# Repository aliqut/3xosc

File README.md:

# 3xOsc
3xOsc | 3 VCO Eurorack Module

This is a Eurorack format VCO synth module, based on Moritz Klein's VCO design.

The module was designed using KiCad.

---

**Features**:

Each of the 3 oscillators has:
  - Coarse and fine tuning knobs
  - a PWM (Pulse-width Modulation) knob
  - a FM (Frequency Modulation) knob and CV (Control Voltage) input

Controls unique to each oscillator:
- Oscillator 1:
  - Saw/Pulse switch
- Oscillator 2:
  - Saw/Pulse wave mix knob
- Oscillator 3:
  - Saw/Pulse switch
  - PWM modulation input, and modulation amount knob 

# Build Guide

1. Download the Gerber files from each board's '.gerbers' folder.
2. If you want to make any modifications to the schematics, download the schematics, make your modifications, and regenerate new Gerbers
3. View the components required from the `BOM.csv` file. (If you have made any changes to the schematics, it is best to regenerate the BOMs).
4. Order all the components needed
5. Send the Gerber files for PCB manufacturing, you can use [PCBShopper](https://pcbshopper.com/) to compare prices across various manufacturers.
6. Assemble the module

- **Notes**
  - Generic 1/4W 1% resistors will work for the build. 
  - The potentiometers are all linear.
    - For the coarse tuning knobs, you can use logarithmic pots if you prefer.
  - In addition to the components in the BOM, you will need M3 bolts to mount the module into your case, and hex nuts to mount the front panel onto the components (these usually come packaged with all the interface components).

Once you have your PCBs and components, refer to the BOM and schematic to solder the components onto the board.

The module is split into three boards, the main board, the connector board, and the front panel. You can make your own front panel if you'd prefer. 

The front panel board has no electrical connections and is purely aesthetic. I recommend letting your PCB manufacturer know this to avoid any issues.

The main and connector board are connected via the pin headers on the top and bottom of the PCBs, make sure you orient the pin headers properly before soldering. The front panel is secured onto the connector board using hex nuts.

### Front Panel

_To view the front panel on KiCad, you need to install the fonts in the `fonts/` folder from this repo, or replace them with your font of choice._

To get the shiny gold finish for the exposed copper used for text/graphics, make sure you get your PCB manufactured with an ENIG finish. Most PCB manufacturers offer this as an option.

I went for a black solder mask, but you get the option to choose from many different colours when ordering your PCB.

# Contributing

Pull requests are the best way to propose changes to the schematics.

1. Fork the repo and create your branch from `master`.
2. Make your changes to the design.
3. If your change directly affects the module's functionality, update the documentation.
4. Issue pull request

## Any contributions you make will be under the GPL Software License

In short, when you submit code changes, your submissions are understood to be under the same GPL license that covers the project.

## Report issues using Github's Issues tab.

I use GitHub issues to track public bugs. Report a bug by opening a new issue.

**Issue Reports** tend to have:

- A quick summary and/or background
- Steps to reproduce
  - Be specific
- What you expected would happen
- What actually happens
- Notes (possibly including why you think this might be happening, or stuff you tried that didn't work)

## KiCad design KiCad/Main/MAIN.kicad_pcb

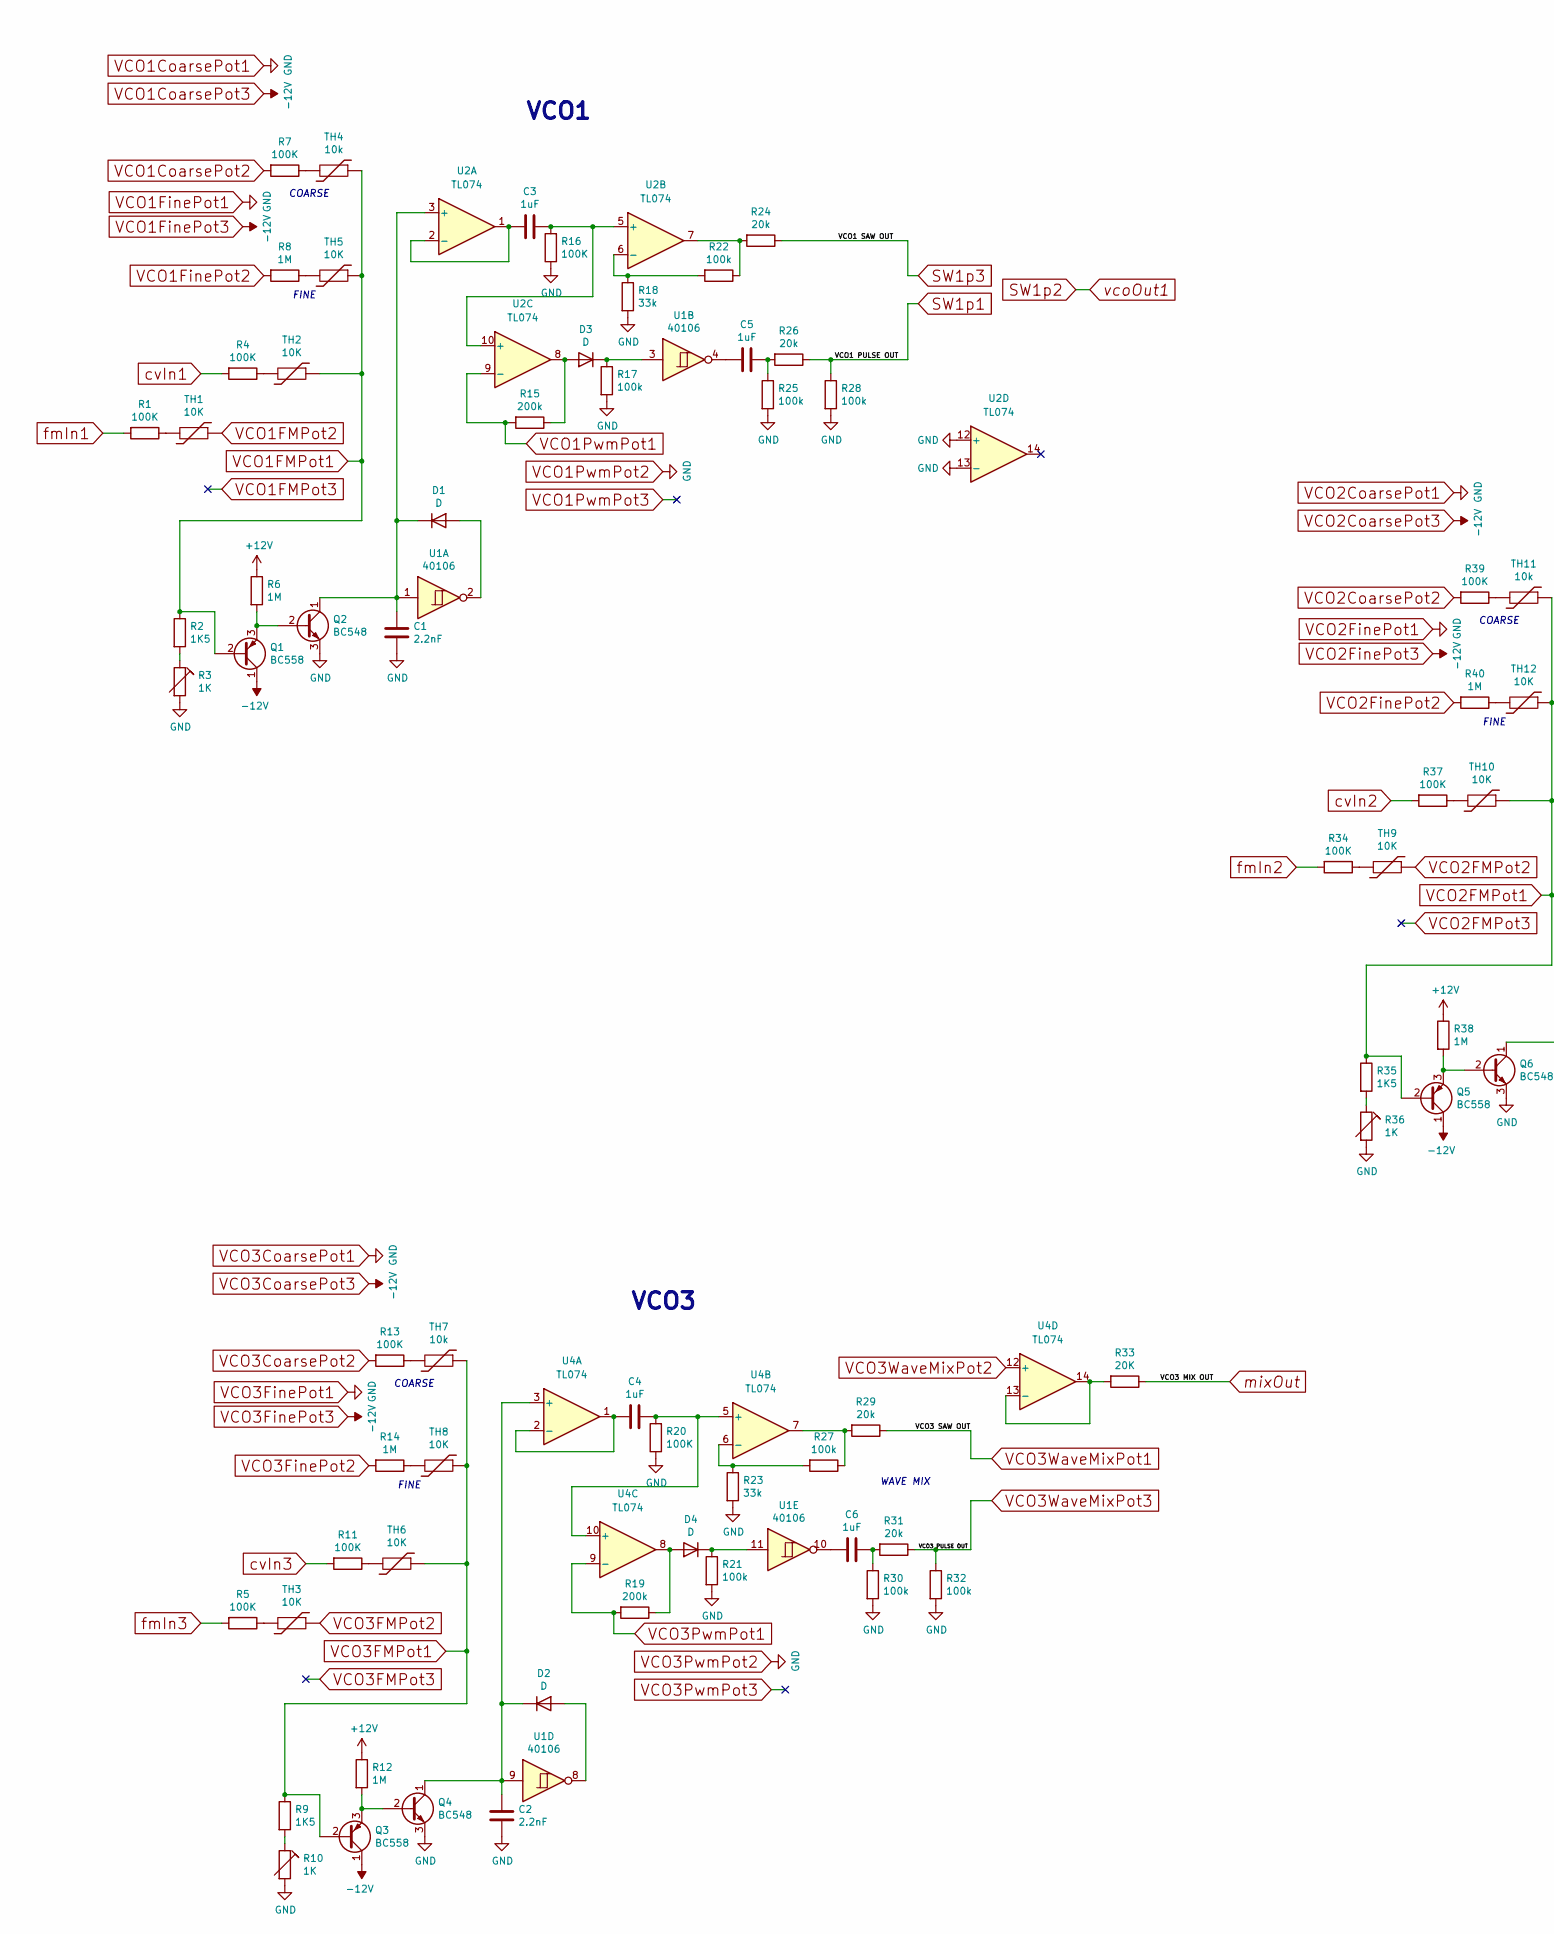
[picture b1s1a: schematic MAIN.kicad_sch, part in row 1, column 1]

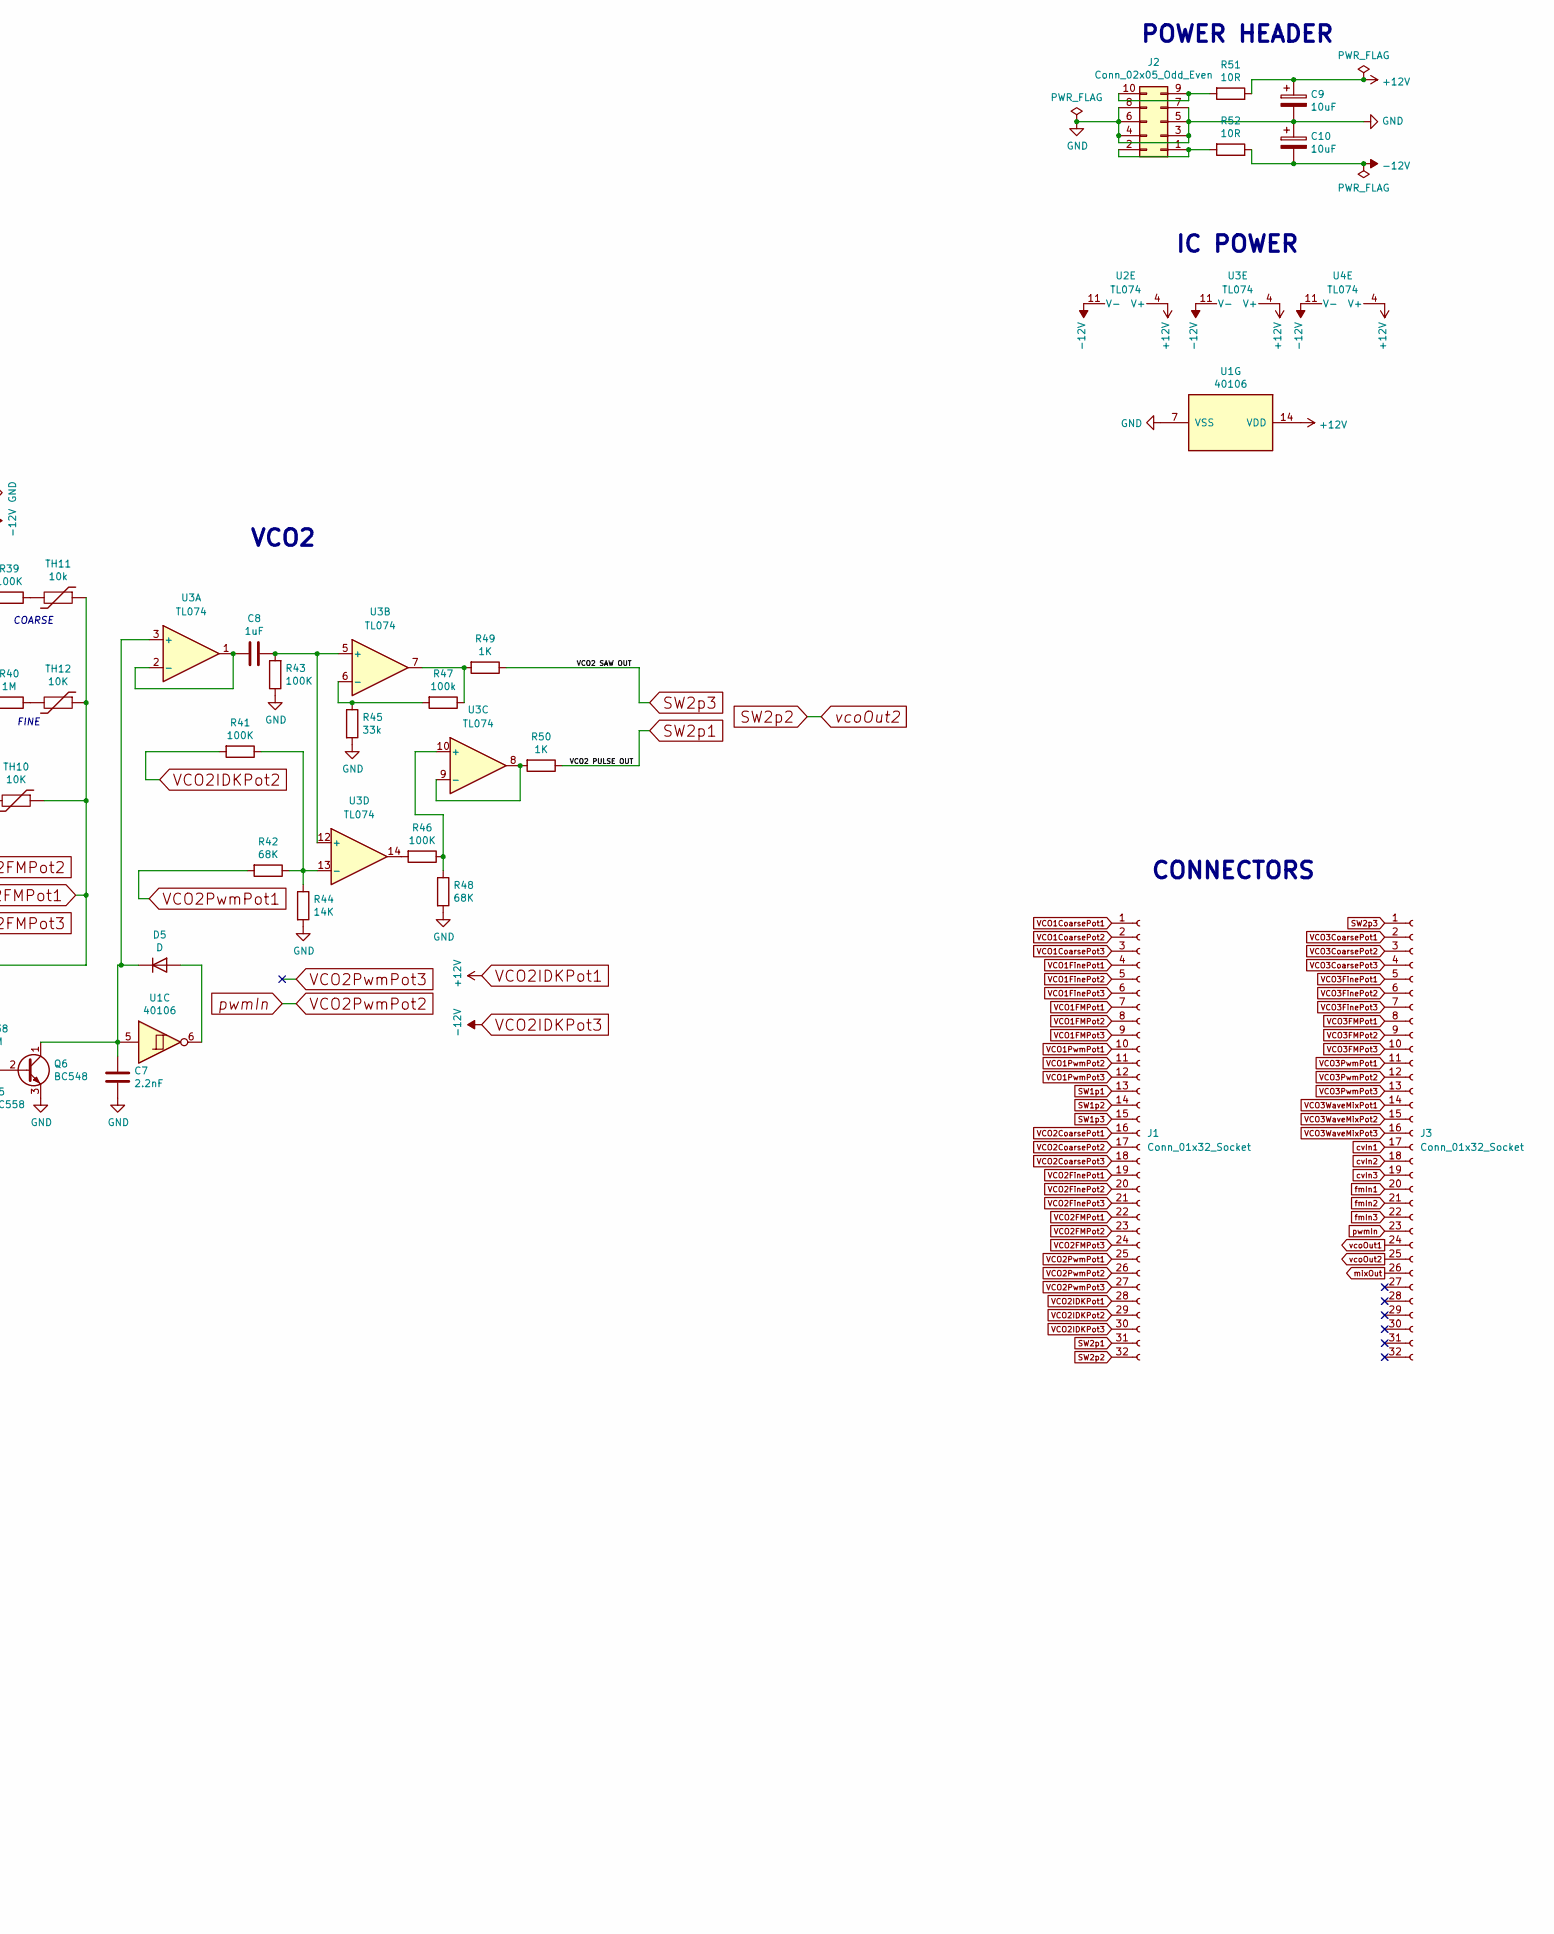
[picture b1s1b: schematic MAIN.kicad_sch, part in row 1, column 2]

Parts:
C1, C2, C7: 2.2nF; C_Disc_D4.7mm_W2.5mm_P5.00mm
C3, C4, C5, C6, C8: 1uF; C_Disc_D3.0mm_W1.6mm_P2.50mm
C9, C10: 10uF; CP_Radial_D5.0mm_P2.00mm
D1, D2, D3, D4, D5: D; D_DO-15_P5.08mm_Vertical_AnodeUp
J1, J3: Conn_01x32_Socket; PinHeader_1x32_P2.54mm_Vertical
J2: Conn_02x05_Odd_Even; PinHeader_2x05_P2.54mm_Vertical
Q1, Q3, Q5: BC558; TO-92_Inline
Q2, Q4, Q6: BC548; TO-92_Inline
R1, R4, R5, R7, R11, R13, R16, R20, R34, R37, R39, R41, R43, R46: 100K; R_Axial_DIN0309_L9.0mm_D3.2mm_P12.70mm_Horizontal
R2, R9, R35: 1K5; R_Axial_DIN0207_L6.3mm_D2.5mm_P10.16mm_Horizontal
R3, R10, R36: 1K; Potentiometer_Bourns_3006Y_Horizontal
R6, R8, R12, R14, R38, R40: 1M; R_Axial_DIN0207_L6.3mm_D2.5mm_P7.62mm_Horizontal
R15, R19: 200k; R_Axial_DIN0207_L6.3mm_D2.5mm_P10.16mm_Horizontal
R17, R21, R22, R25, R27, R28, R30, R32, R47: 100k; R_Axial_DIN0309_L9.0mm_D3.2mm_P12.70mm_Horizontal
R18, R23, R45: 33k; R_Axial_DIN0207_L6.3mm_D2.5mm_P10.16mm_Horizontal
R24, R26, R29, R31: 20k; R_Axial_DIN0207_L6.3mm_D2.5mm_P7.62mm_Horizontal
R33: 20K; R_Axial_DIN0207_L6.3mm_D2.5mm_P7.62mm_Horizontal
R42, R48: 68K; R_Axial_DIN0207_L6.3mm_D2.5mm_P10.16mm_Horizontal
R44: 14K; R_Axial_DIN0207_L6.3mm_D2.5mm_P10.16mm_Horizontal
R49, R50: 1K; R_Axial_DIN0207_L6.3mm_D2.5mm_P10.16mm_Horizontal
R51, R52: 10R; R_Axial_DIN0207_L6.3mm_D2.5mm_P10.16mm_Horizontal
TH1, TH2, TH3, TH5, TH6, TH8, TH9, TH10, TH12: 10K; R_Axial_DIN0204_L3.6mm_D1.6mm_P2.54mm_Vertical
TH4, TH7, TH11: 10k; R_Axial_DIN0204_L3.6mm_D1.6mm_P2.54mm_Vertical
U1: 40106; DIP-14_W7.62mm_Socket
U2, U3, U4: TL074; DIP-14_W7.62mm_Socket

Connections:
unnamed: C5.1, R25.1, R26.2
unnamed: C5.2, U1.4
unnamed: C6.1, R30.1, R31.2
unnamed: C6.2, U1.10
unnamed: D1.2 (A), U1.2
unnamed: C1.1, D1.1 (K), Q2.1 (C), U1.1, U2.3 (+)
unnamed: D2.2 (A), U1.8
unnamed: C2.1, D2.1 (K), Q4.1 (C), U1.9, U4.3 (+)
unnamed: D3.2 (A), R15.1, U2.8
unnamed: D3.1 (K), R17.1, U1.3
unnamed: D4.2 (A), R19.1, U4.8
unnamed: D4.1 (K), R21.1, U1.11
unnamed: D5.2 (A), U1.6
unnamed: C7.1, D5.1 (K), Q6.1 (C), U1.5, U3.3 (+)
unnamed: J2.1, J2.2, R52.2
unnamed: J2.9, J2.10, R51.2
unnamed: Q1.3 (E), Q2.2 (B), R6.2
unnamed: Q3.3 (E), Q4.2 (B), R12.2
unnamed: Q5.3 (E), Q6.2 (B), R38.2
unnamed: R1.1, TH1.2
unnamed: R2.2, R3.1
unnamed: R4.1, TH2.2
unnamed: R5.1, TH3.2
unnamed: R7.1, TH4.2
unnamed: R8.1, TH5.2
unnamed: R9.2, R10.1
unnamed: R11.1, TH6.2
unnamed: R13.1, TH7.2
unnamed: R14.1, TH8.2
unnamed: R22.1, R24.2, U2.7
unnamed: R27.1, R29.2, U4.7
unnamed: R34.1, TH9.2
unnamed: R35.2, R36.1
unnamed: R37.1, TH10.2
unnamed: R39.1, TH11.2
unnamed: R40.1, TH12.2
unnamed: R46.2, U3.14
unnamed: R47.1, R49.2, U3.7
unnamed: C3.2, U2.1, U2.2 (-)
unnamed: C3.1, R16.2, U2.5 (+), U2.10 (+)
unnamed: R18.1, R22.2, U2.6 (-)
unnamed: C8.2, U3.1, U3.2 (-)
unnamed: C8.1, R43.2, U3.5 (+), U3.12 (+)
unnamed: R45.1, R47.2, U3.6 (-)
unnamed: R46.1, R48.1, U3.10 (+)
unnamed: R50.2, U3.8, U3.9 (-)
unnamed: R41.1, R42.1, R44.1, U3.13 (-)
unnamed: C4.2, U4.1, U4.2 (-)
unnamed: C4.1, R20.2, U4.5 (+), U4.10 (+)
unnamed: R23.1, R27.2, U4.6 (-)
unnamed: R33.2, U4.13 (-), U4.14
SW1p1: J1.13, R26.1, R28.1
SW1p2: J1.14, J3.24
SW1p3: J1.15, R24.1
SW2p1: J1.31, R50.1
SW2p2: J1.32, J3.25
SW2p3: J3.1, R49.1
VCO1CoarsePot1: C1.2, C2.2, C7.2, C9.2, C10.1, J1.1, J1.4, J1.11, J1.16, J1.19, J2.3, J2.4, J2.5, J2.6, J2.7, J2.8, J3.2, J3.5, J3.12, Q2.3 (E), Q4.3 (E), Q6.3 (E), R3.2, R10.2, R16.1, R17.2, R18.2, R20.1, R21.2, R23.2, R25.2, R28.2, R30.2, R32.2, R36.2, R43.1, R44.2, R45.2, R48.2, U1.7 (VSS), U2.12 (+), U2.13 (-)
VCO1CoarsePot2: J1.2, R7.2
VCO1CoarsePot3: C10.2, J1.3, J1.6, J1.18, J1.21, J1.30, J3.4, J3.7, Q1.1 (C), Q3.1 (C), Q5.1 (C), R52.1, U2.11 (V-), U3.11 (V-), U4.11 (V-)
VCO1FMPot1: J1.7, Q1.2 (B), R2.1, TH2.1, TH4.1, TH5.1
VCO1FMPot2: J1.8, TH1.1
VCO1FMPot3: J1.9
VCO1FinePot2: J1.5, R8.2
VCO1PwmPot1: J1.10, R15.2, U2.9 (-)
VCO1PwmPot3: J1.12
VCO2CoarsePot2: J1.17, R39.2
VCO2FMPot1: J1.22, Q5.2 (B), R35.1, TH10.1, TH11.1, TH12.1
VCO2FMPot2: J1.23, TH9.1
VCO2FMPot3: J1.24
VCO2FinePot2: J1.20, R40.2
VCO2IDKPot1: C9.1, J1.28, R6.1, R12.1, R38.1, R51.1, U1.14 (VDD), U2.4 (V+), U3.4 (V+), U4.4 (V+)
VCO2IDKPot2: J1.29, R41.2
VCO2PwmPot1: J1.25, R42.2
VCO2PwmPot2: J1.26, J3.23
VCO2PwmPot3: J1.27
VCO3CoarsePot2: J3.3, R13.2
VCO3FMPot1: J3.8, Q3.2 (B), R9.1, TH6.1, TH7.1, TH8.1
VCO3FMPot2: J3.9, TH3.1
VCO3FMPot3: J3.10
VCO3FinePot2: J3.6, R14.2
VCO3PwmPot1: J3.11, R19.2, U4.9 (-)
VCO3PwmPot3: J3.13
VCO3WaveMixPot1: J3.14, R29.1
VCO3WaveMixPot2: J3.15, U4.12 (+)
VCO3WaveMixPot3: J3.16, R31.1, R32.1
cvIn1: J3.17, R4.2
cvIn2: J3.18, R37.2
cvIn3: J3.19, R11.2
fmIn1: J3.20, R1.2
fmIn2: J3.21, R34.2
fmIn3: J3.22, R5.2
mixOut: J3.26, R33.1

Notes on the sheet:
WAVE MIX
COARSE
VCO1
FINE
VCO3
IC POWER
POWER HEADER
CONNECTORS
VCO2

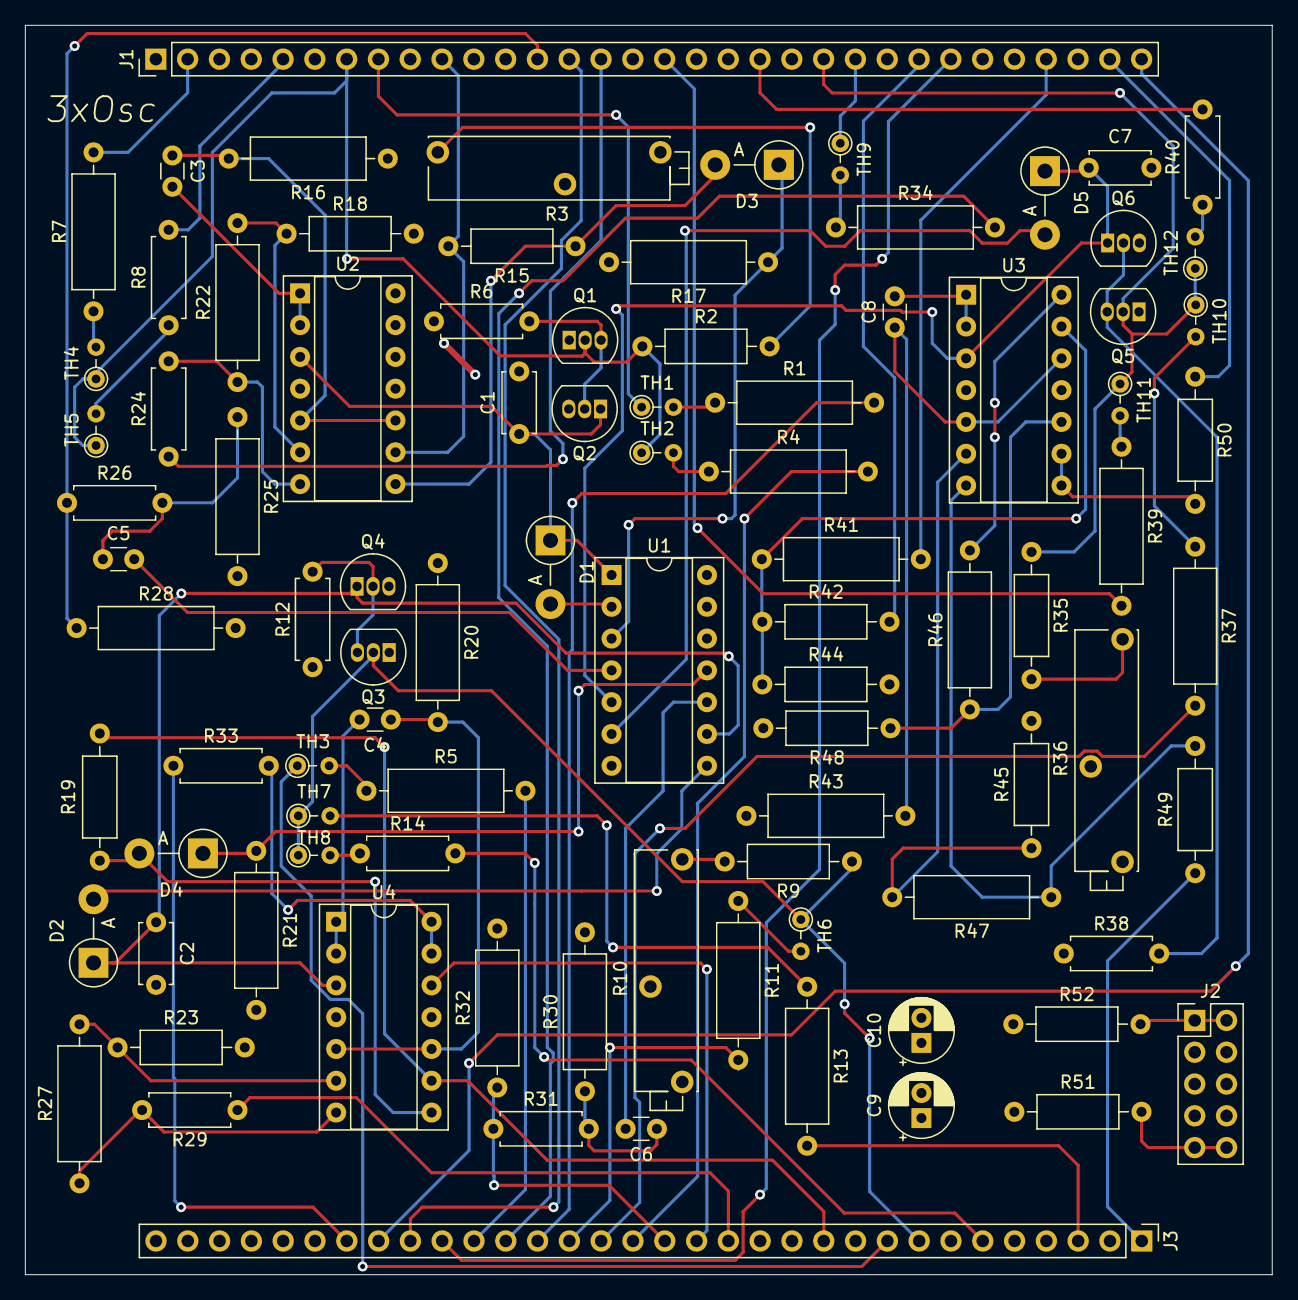
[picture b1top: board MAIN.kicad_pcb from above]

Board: 4 copper layers, 99.6 x 99.8 mm, 92 parts (0 on the bottom side), 87 nets.

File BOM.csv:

MAIN BOARD,,,,,
#,Reference,Qty,Value,Component/Footprint,Notes
1,"C1, C2, C7",3,2.2nF,Disc capacitor: D4.7mm_W2.5mm_P5.00mm,All components are through hole
2,"C3, C4, C5, C6, C8",5,1uF,Disc capacitor: D3.0mm_W1.6mm_P2.50mm,
3,"C9, C10",2,10uF,Electrolitic capacitor :CP_Radial_D5.0mm_P2.00mm,
4,"D1, D2, D3, D4, D5",5,DO-15,DO-15 P5.08mm Vertical AnodeUp,
5,"J1, J3",2,Conn 01x32 Socket,Connector_PinHeader_2.54mm:PinHeader 1x32,Buy a pair of male and female headers. This is for connecting the main board to the connector board.
6,J2,1,Conn 02x05 Odd_Even,Connector_PinHeader_2.54mm:PinHeader 2x05,"Eurorack power header, keyed box 02x05 pin header"
7,"Q1, Q3, Q5",3,BC558 Transistor,THT TO-92_Inline,
8,"Q2, Q4, Q6",3,BC548 Transistor,THT TO-92_Inline,
9,"R1, R4, R5, R7, R11, R13, R16, R20, R34, R37, R39, R41, R43, R46, R17, R21, R22, R25, R27, R28, R30, R32, R47",23,100K,Metalic film resistor 1/4W L9.0mm_D3.2mm_P12.70mm_Horizontal,
10,"R2, R9, R35",3,1K5,Metalic film resistor 1/4W L6.3mm_D2.5mm_P10.16mm_Horizontal,
11,"R3, R10, R36",3,1K,Potentiometer Bourns 3006Y Horizontal,
12,"R6, R8, R12, R14, R38, R40",6,1M,Metalic film resistor 1/4W,
13,"R15, R19",2,200K,Metalic film resistor 1/4W,
14,"R18, R23, R45",3,33K,Metalic film resistor 1/4W,
15,"R24, R26, R29, R31, R33",5,20K,Metalic film resistor 1/4W,
16,"R42, R48",2,68K,Metalic film resistor 1/4W,
17,R44,1,14K,Metalic film resistor 1/4W,
18,"R49, R50",2,1K,Metalic film resistor 1/4W,
19,"R51, R52",2,10R,Metalic film resistor 1/4W,
20,"TH1, TH2, TH3, TH5, TH6, TH8, TH9, TH10, TH12, TH4, TH7, TH11",12,10K,Disk NTC Thermistor,
21,U1,1,40106,40106 Schmitt Trigger Inverter IC THT,
22,"U2, U3, U4",3,TL074,TL074 Op-Amp IC THT,
,,,,,
,,,,,
,,,,,
,,,,,
CONNECTOR BOARD,,,,,
#,Reference,Qty,Value,,Notes
1,"J1, J2",2,Conn_01x32_Socket,2.54mm 01x32,
2,"J3, J4, J5, J6, J7, J8, J9, J10, J11, J12",10,Audio Jacks,Thonk AudioJacks:Jack 3.5mm QingPu WQP-PJ366ST Vertical,Thonkiconn Jack Sockets or clones
3,"RV1, RV4, RV5, RV9, RV10, RV14",6,100K,Potentiometer Alpha RD901F-40-00D Vertical Linear,Tuning pots. You can replace the coarse tuning pots with logarithmic ones if you prefer
4,"RV2, RV3, RV6, RV7, RV11, RV12, RV13",7,1M,Potentiometer Alpha RD901F-40-00D Vertical Linear,
5,RV8,1,250K,Potentiometer Alpha RD901F-40-00D Vertical Linear,PWM Pot
6,"SW1, SW2",2,SPDT Switch,SPDT-ON-ON,SPDT. These have three legs.
7,"U1, U2, U3, U4",4,DIP Socket IC 7x2,DIP Sockets for IC 7x2,"Heavily recommended. Makes it easy to swap out ICs if you're troubleshooting, and protects the ICs from heat during soldering."

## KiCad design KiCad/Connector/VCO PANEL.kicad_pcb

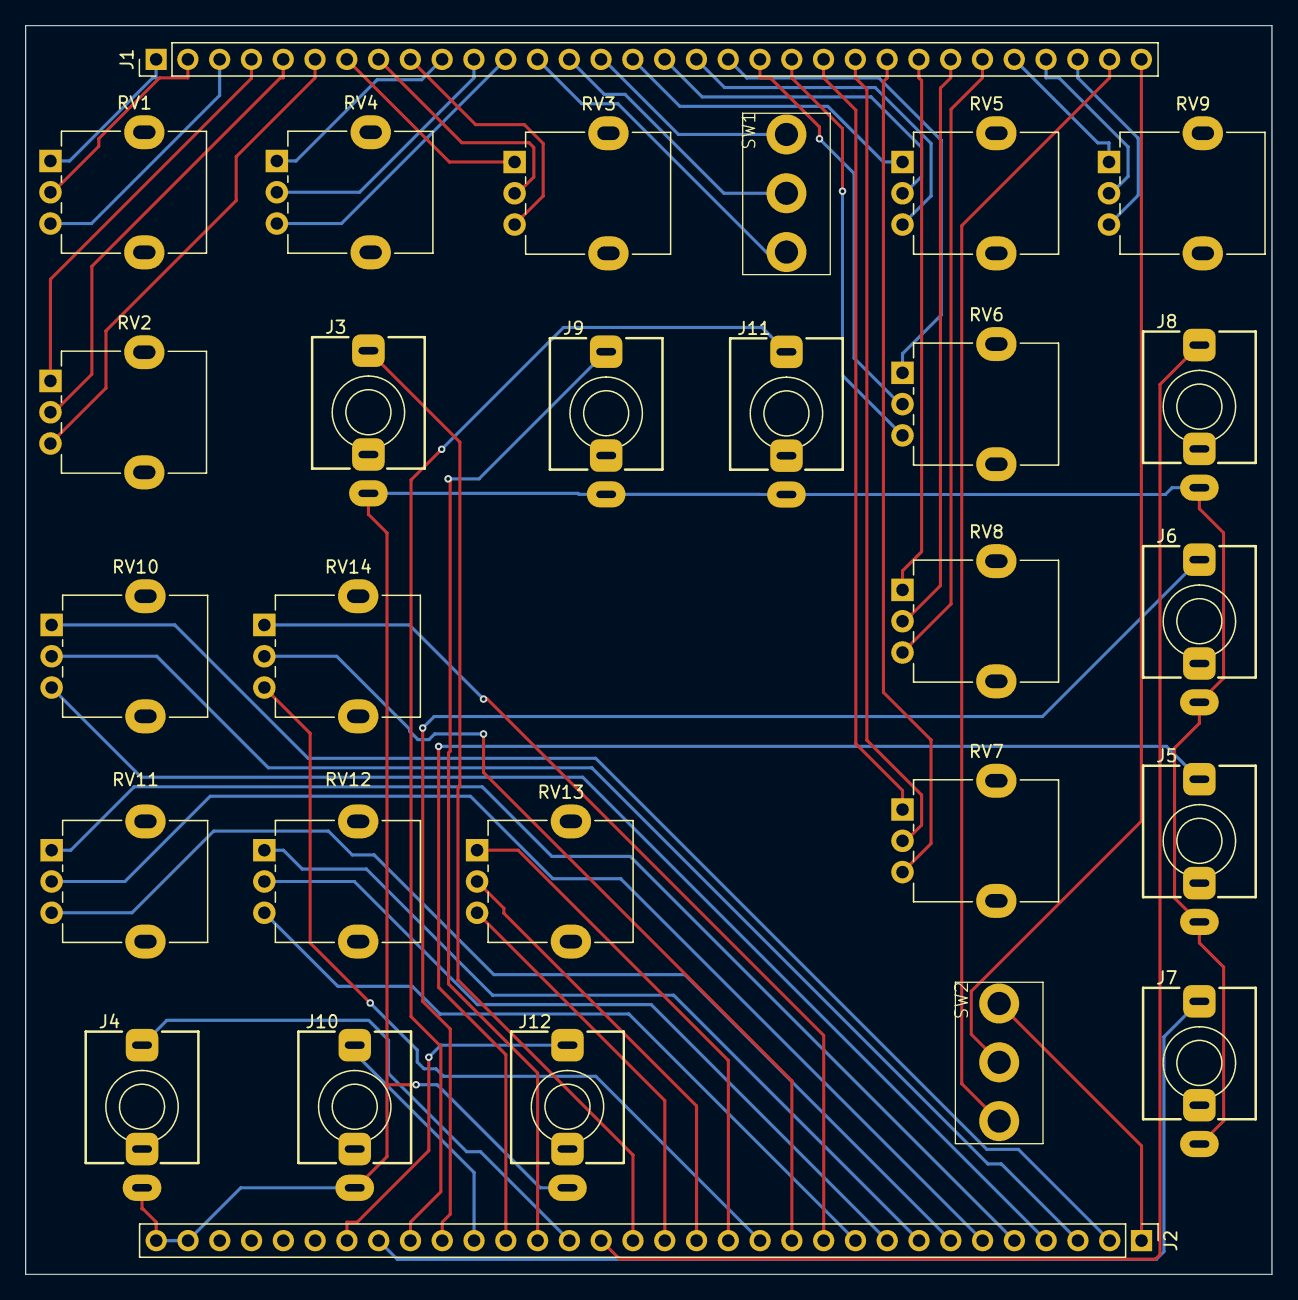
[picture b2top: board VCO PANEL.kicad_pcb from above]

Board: 2 copper layers, 99.6 x 99.8 mm, 28 parts (0 on the bottom side), 59 nets.

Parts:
J1, J2: Conn_01x32_Socket; PinHeader_1x32_P2.54mm_Vertical
J3, J4, J5, J6, J7, J8, J9, J10, J11, J12: AudioJack3; Jack_3.5mm_QingPu_WQP-PJ366ST_Vertical
RV1, RV4, RV5, RV9, RV10, RV14: 100k; Potentiometer_Alpha_RD901F-40-00D_Single_Vertical
RV2, RV3, RV6, RV7, RV11, RV12, RV13: 1M; Potentiometer_Alpha_RD901F-40-00D_Single_Vertical
RV8: 250k; Potentiometer_Alpha_RD901F-40-00D_Single_Vertical
SW1, SW2: SW_SPDT; DWB1-SPDT-ON-ON

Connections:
Ground: J2.31, J2.32, J3.S, J4.S, J5.S, J6.S, J7.S, J8.S, J9.S, J10.S, J11.S, J12.S
SW1p1: J1.13, SW1.1 (A)
SW1p2: J1.14, SW1.2 (B)
SW1p3: J1.15, SW1.3 (C)
SW2p1: J1.31, SW2.1 (A)
SW2p2: J1.32, SW2.2 (B)
SW2p3: J2.1, SW2.3 (C)
VCO1CoarsePot1: J1.1, RV1.1
VCO1CoarsePot2: J1.2, RV1.2
VCO1CoarsePot3: J1.3, RV1.3
VCO1FMPot1: J1.7, RV3.1
VCO1FMPot2: J1.8, RV3.2
VCO1FMPot3: J1.9, RV3.3
VCO1FinePot1: J1.4, RV2.1
VCO1FinePot2: J1.5, RV2.2
VCO1FinePot3: J1.6, RV2.3
VCO1PwmPot1: J1.10, RV4.1
VCO1PwmPot2: J1.11, RV4.2
VCO1PwmPot3: J1.12, RV4.3
VCO2CoarsePot1: J1.16, RV5.1
VCO2CoarsePot2: J1.17, RV5.2
VCO2CoarsePot3: J1.18, RV5.3
VCO2FMPot1: J1.22, RV7.1
VCO2FMPot2: J1.23, RV7.2
VCO2FMPot3: J1.24, RV7.3
VCO2FinePot1: J1.19, RV6.1
VCO2FinePot2: J1.20, RV6.2
VCO2FinePot3: J1.21, RV6.3
VCO2IDKPot1: J1.28, RV9.1
VCO2IDKPot2: J1.29, RV9.2
VCO2IDKPot3: J1.30, RV9.3
VCO2PwmPot1: J1.25, RV8.1
VCO2PwmPot2: J1.26, RV8.2
VCO2PwmPot3: J1.27, RV8.3
VCO3CoarsePot1: J2.2, RV10.1
VCO3CoarsePot2: J2.3, RV10.2
VCO3CoarsePot3: J2.4, RV10.3
VCO3FMPot1: J2.8, RV12.1
VCO3FMPot2: J2.9, RV12.2
VCO3FMPot3: J2.10, RV12.3
VCO3FinePot1: J2.5, RV11.1
VCO3FinePot2: J2.6, RV11.2
VCO3FinePot3: J2.7, RV11.3
VCO3PwmPot1: J2.11, RV14.1
VCO3PwmPot2: J2.12, RV14.2
VCO3PwmPot3: J2.13, RV14.3
VCO3WaveMixPot1: J2.14, RV13.1
VCO3WaveMixPot2: J2.15, RV13.2
VCO3WaveMixPot3: J2.16, RV13.3
cvIn1: J2.17, J3.T
cvIn2: J2.18, J8.T
cvIn3: J2.19, J4.T
fmIn1: J2.20, J9.T
fmIn2: J2.21, J5.T
fmIn3: J2.22, J10.T
mixOut: J2.26, J12.T
pwmIn: J2.23, J6.T
vcoOut1: J2.24, J11.T
vcoOut2: J2.25, J7.T

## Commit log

2024-07-12 uploaded gerber files
2024-07-12 uploaded KiCad files
2024-07-12 uploaded render
2024-07-12 uploaded fonts for front panel
2024-07-12 updated main board PCB file, there were some unconnected pins
2024-07-12 added audio jack libraries to repo
2024-10-02 docs: add schematic PDFs
2024-10-03 refactor: Change main schematic to Op-Amp per VCO. Add net labels for VCO outputs
2025-01-11 refactor: Rename KiCad files
2025-01-11 feat: Add BOM CSV
2025-01-11 fix: Regenerate gerbers
2025-01-12 docs: Update README.md
2025-01-16 fix: Missing PCB traces in main board project & gerbers
2025-02-19 docs: Upload gerber zip files
2025-03-13 refactor: Rework Main board PCB
2025-03-13 docs: Update gerber zips
2025-07-12 Update BOM
